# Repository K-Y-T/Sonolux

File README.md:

# Sonolux

Sonolux is an ongoing personal engineering project exploring the intersection of analogue electronics, embedded systems, signal processing, and software for music visualisation.

Originally inspired by a university assignment involving a three-band analogue frequency display, the project has since evolved into a broader platform for developing hardware and software related to audio signal analysis and visualisation.

---

## Current Status

The repository currently contains:

- Sound2Light prototype (breadboard implementation)
- Sonolux V1 analogue hardware design
- Circuit schematics
- PCB design files

The project is under active development and will continue to evolve throughout my undergraduate studies.

---

## Project Goals

Current long-term objectives include:

- Five-band analogue frequency visualisation
- Analogue Speaker system
- Custom PCB design
- Embedded control and power management
- Bluetooth audio integration
- JUCE-based desktop software

## What it uses

Current Development Areas

- Analogue Electronics
- PCB Design
- Autodesk Fusion
- Multisim

Future Development

- Embedded C/C++
- ESP32
- JUCE
- Digital Signal Processing

---

## Project Philosophy

Rather than being treated as a single coursework project, Sonolux serves as a long-term engineering platform through which I explore progressively more advanced concepts in electronics, embedded systems, and audio technology.

---

## Status

🟡 Active Development

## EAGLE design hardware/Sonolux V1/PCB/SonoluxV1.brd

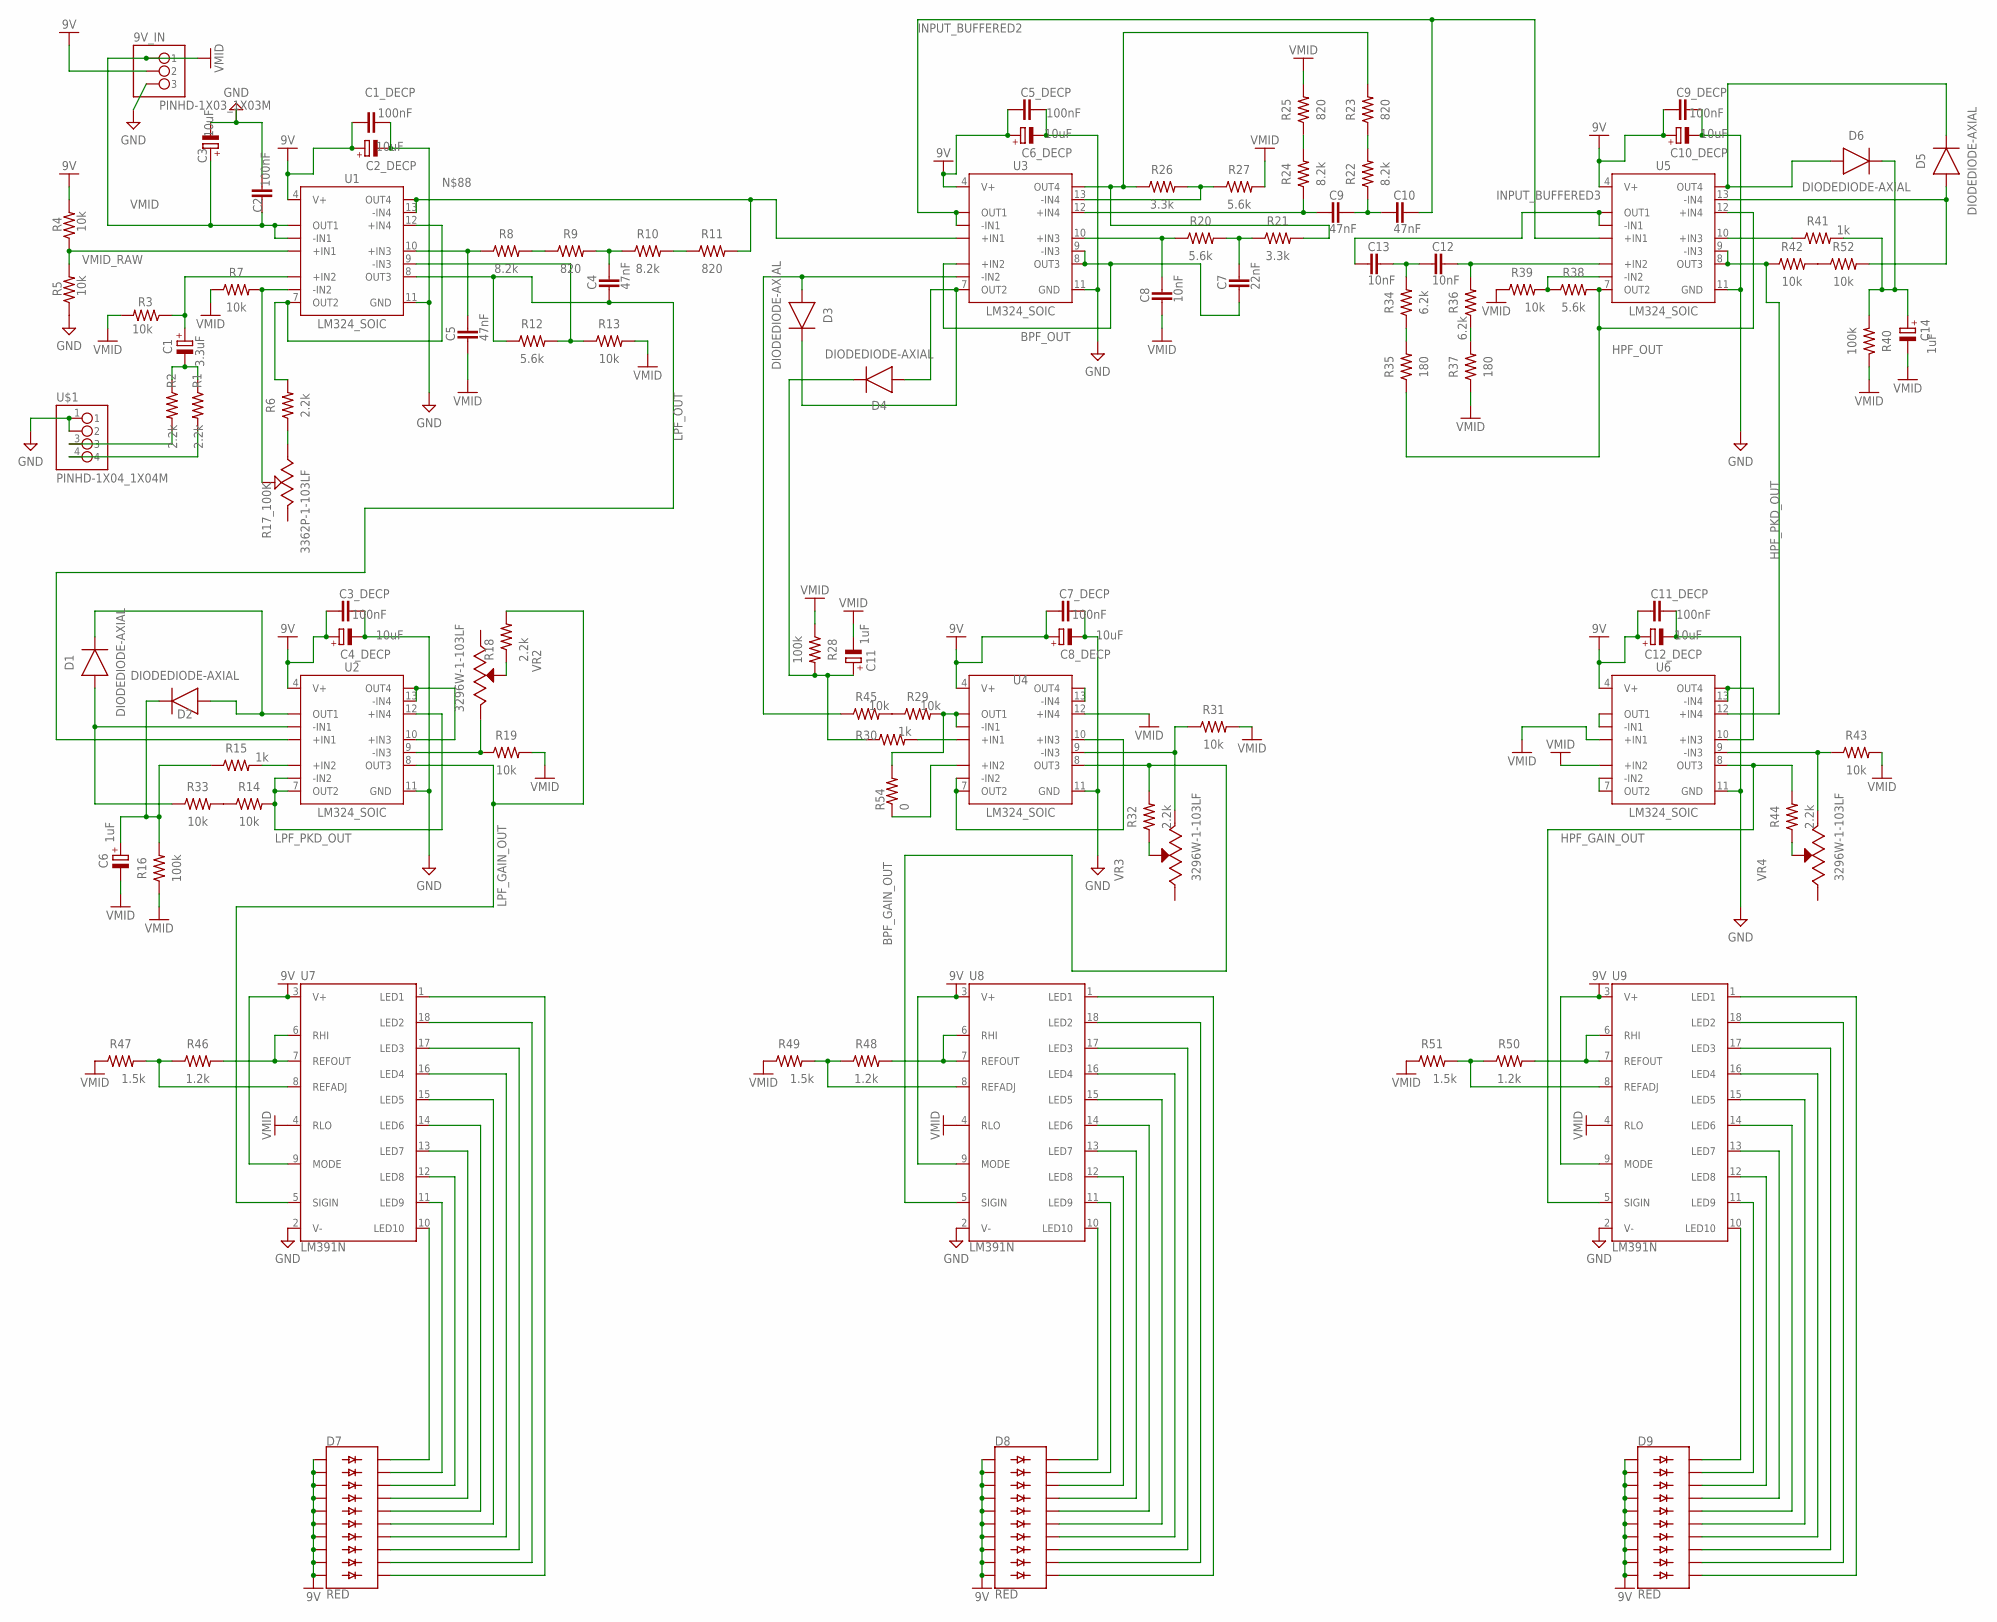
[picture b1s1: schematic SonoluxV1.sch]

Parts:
9V_IN: PINHD-1X03_1X03M; 1X03
C1: 3.3uF; CAPPRD254W65D500H1150B
C1_DECP, C2, C3_DECP, C5_DECP, C7_DECP, C9_DECP, C11_DECP: 100nF; CAP-THRU-2.54MM
C2_DECP, C3, C4_DECP, C6_DECP, C8_DECP, C10_DECP, C12_DECP: 10uF; CAPPRD254W65D500H1150B
C4, C5, C9, C10: 47nF; CAP-THRU-2.54MM
C6, C11, C14: 1uF; CAPPRD254W65D500H1150B
C7: 22nF; CAP-THRU-2.54MM
C8, C12, C13: 10nF; CAP-THRU-2.54MM
D1, D2, D3, D4, D5, D6: DIODEDIODE-AXIAL; DIODE-AXIAL
D7, D8, D9: RED; LED_BARGRAPH_10
R1, R2, R6, R18, R32, R44: 2.2k; RESAD724W46L381D178B
R3, R4, R5, R7, R13, R14, R19, R29, R31, R33, R39, R42, R43, R45, R52: 10k; RESAD724W46L381D178B
R8, R10, R22, R24: 8.2k; RESAD724W46L381D178B
R9, R11, R23, R25: 820; RESAD724W46L381D178B
R12, R20, R27, R38: 5.6k; RESAD724W46L381D178B
R15, R30, R41: 1k; RESAD724W46L381D178B
R16, R28, R40: 100k; RESAD724W46L381D178B
R17_100K: 3362P-1-103LF
R21, R26: 3.3k; RESAD724W46L381D178B
R34, R36: 6.2k; RESAD724W46L381D178B
R35, R37: 180; RESAD724W46L381D178B
R46, R48, R50: 1.2k; RESAD724W46L381D178B
R47, R49, R51: 1.5k; RESAD724W46L381D178B
R54: 0; RESAD724W46L381D178B
U1, U2, U3, U4, U5, U6: LM324_SOIC; SOIC127P600X175-14N
U7, U8, U9: LM391N; DIL18
U$1: PINHD-1X04_1X04M; 1X04
VR2, VR3, VR4: 3296W-1-103LF; TRIM_3296W-1-103LF

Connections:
9V: 9V_IN.2, C1_DECP.2, C2_DECP.1 (+), C3_DECP.2, C4_DECP.1 (+), C5_DECP.2, C6_DECP.1 (+), C7_DECP.2, C8_DECP.1 (+), C9_DECP.2, C10_DECP.1 (+), C11_DECP.2, C12_DECP.1 (+), D7.1 (A), D7.2 (A1), D7.3 (A2), D7.4 (A3), D7.5 (A4), D7.6 (A5), D7.7 (A6), D7.8 (A7), D7.9 (A8), D7.10 (A9), D8.1 (A), D8.2 (A1), D8.3 (A2), D8.4 (A3), D8.5 (A4), D8.6 (A5), D8.7 (A6), D8.8 (A7), D8.9 (A8), D8.10 (A9), D9.1 (A), D9.2 (A1), D9.3 (A2), D9.4 (A3), D9.5 (A4), D9.6 (A5), D9.7 (A6), D9.8 (A7), D9.9 (A8), D9.10 (A9), R4.2, U1.4 (V+), U2.4 (V+), U3.4 (V+), U4.4 (V+), U5.4 (V+), U6.4 (V+), U7.3 (V+), U7.9 (MODE), U8.3 (V+), U8.9 (MODE), U9.3 (V+), U9.9 (MODE)
BPF_GAIN_OUT: R32.2, U4.8 (OUT3), U8.5 (SIGIN)
BPF_OUT: C7.2, U3.5 (+IN2), U3.8 (OUT3), U3.9 (-IN3)
BPF_PKD_OUT: R29.2, R54.2, U4.1 (OUT1), U4.2 (-IN1)
GND: 9V_IN.3, C1_DECP.1, C2.1, C2_DECP.2 (-), C3.2 (-), C3_DECP.1, C4_DECP.2 (-), C5_DECP.1, C6_DECP.2 (-), C7_DECP.1, C8_DECP.2 (-), C9_DECP.1, C10_DECP.2 (-), C11_DECP.1, C12_DECP.2 (-), R5.1, U1.11 (GND), U2.11 (GND), U3.11 (GND), U4.11 (GND), U5.11 (GND), U6.11 (GND), U7.2 (V-), U8.2 (V-), U9.2 (V-), U$1.1, U$1.2
HPF_GAIN_OUT: R44.2, U6.8 (OUT3), U9.5 (SIGIN)
HPF_OUT: R35.1, R38.2, U5.7 (OUT2), U5.12 (+IN4)
HPF_PKD_OUT: R42.1, U5.8 (OUT3), U5.9 (-IN3), U6.12 (+IN4)
INPUT_BUFFERED2: C10.1, U3.1 (OUT1), U3.2 (-IN1), U5.3 (+IN1)
INPUT_BUFFERED3: C13.2, U5.1 (OUT1), U5.2 (-IN1)
INPUT_FILTERED: C1.1 (+), R3.1, U1.5 (+IN2)
INPUT_GAINED: R6.2, U1.7 (OUT2), U1.12 (+IN4)
INPUT_MONO: C1.2 (-), R1.1, R2.1
LPF_BUFFERED: U2.10 (+IN3), U2.13 (-IN4), U2.14 (OUT4)
LPF_GAIN_OUT: R18.2, U2.8 (OUT3), U7.5 (SIGIN)
LPF_OUT: C4.2, R12.1, U1.8 (OUT3), U2.3 (+IN1)
LPF_PKD_OUT: R14.2, U2.6 (-IN2), U2.7 (OUT2), U2.12 (+IN4)
unnamed: R6.1, R17_100K.3
unnamed: R7.2, R17_100K.2, U1.6 (-IN2)
unnamed: C5.1, R8.1, U1.10 (+IN3)
unnamed: R8.2, R9.1
unnamed: C4.1, R9.2, R10.1
unnamed: R10.2, R11.1
unnamed: D1.2 (C), D2.1 (A), U2.1 (OUT1)
unnamed: R12.2, R13.1, U1.9 (-IN3)
unnamed: D1.1 (A), R33.1, U2.2 (-IN1)
unnamed: C9.1, C10.2, R22.1
unnamed: C6.1 (+), D2.2 (C), R15.1, R16.2
unnamed: R15.2, U2.5 (+IN2)
unnamed: C8.1, R20.1, U3.10 (+IN3)
unnamed: D5.1 (A), R52.2, U5.13 (-IN4)
unnamed: C7.1, R20.2, R21.1
unnamed: R18.1, VR2.2 (WIPER)
unnamed: R21.2, R23.2, R26.1, U3.14 (OUT4)
unnamed: C9.2, R24.1, U3.12 (+IN4)
unnamed: R22.2, R23.1
unnamed: R24.2, R25.1
unnamed: R26.2, R27.1, U3.13 (-IN4)
unnamed: D3.1 (A), R45.1, U3.6 (-IN2)
unnamed: D3.2 (C), D4.1 (A), U3.7 (OUT2)
unnamed: C11.1 (+), D4.2 (C), R28.2, R30.1
unnamed: R32.1, VR3.2 (WIPER)
unnamed: R30.2, U4.3 (+IN1)
unnamed: U4.6 (-IN2), U4.7 (OUT2), U4.10 (+IN3)
unnamed: R31.1, U4.9 (-IN3), VR3.3 (CW)
unnamed: R38.1, R39.2, U5.6 (-IN2)
unnamed: C12.2, C13.1, R34.2
unnamed: R34.1, R35.2
unnamed: R36.1, R37.2
unnamed: C12.1, R36.2, U5.5 (+IN2)
unnamed: D5.2 (C), D6.1 (A), U5.14 (OUT4)
unnamed: C14.1 (+), D6.2 (C), R40.2, R41.2
unnamed: R46.2, U7.6 (RHI), U7.7 (REFOUT)
unnamed: R41.1, U5.10 (+IN3)
unnamed: U6.10 (+IN3), U6.13 (-IN4), U6.14 (OUT4)
unnamed: R44.1, VR4.2 (WIPER)
unnamed: R43.1, U6.9 (-IN3), VR4.3 (CW)
unnamed: R46.1, R47.2, U7.8 (REFADJ)
unnamed: D7.20 (C), U7.10 (LED10)
unnamed: D7.19 (C1), U7.11 (LED9)
unnamed: D7.18 (C2), U7.12 (LED8)
unnamed: D7.17 (C3), U7.13 (LED7)
unnamed: D7.16 (C4), U7.14 (LED6)
unnamed: D7.15 (C5), U7.15 (LED5)
unnamed: D7.14 (C6), U7.16 (LED4)
unnamed: D7.13 (C7), U7.17 (LED3)
unnamed: D7.12 (C8), U7.18 (LED2)
unnamed: D7.11 (C9), U7.1 (LED1)
unnamed: R48.2, U8.6 (RHI), U8.7 (REFOUT)
unnamed: R48.1, R49.2, U8.8 (REFADJ)
unnamed: D8.20 (C), U8.10 (LED10)
unnamed: D8.19 (C1), U8.11 (LED9)
unnamed: D8.18 (C2), U8.12 (LED8)
unnamed: D8.17 (C3), U8.13 (LED7)
unnamed: D8.16 (C4), U8.14 (LED6)
unnamed: D8.15 (C5), U8.15 (LED5)
unnamed: D8.14 (C6), U8.16 (LED4)
unnamed: D8.13 (C7), U8.17 (LED3)
unnamed: D8.12 (C8), U8.18 (LED2)
unnamed: D8.11 (C9), U8.1 (LED1)
unnamed: R50.2, U9.6 (RHI), U9.7 (REFOUT)
unnamed: R50.1, R51.2, U9.8 (REFADJ)
unnamed: D9.20 (C), U9.10 (LED10)
unnamed: D9.19 (C1), U9.11 (LED9)
unnamed: D9.18 (C2), U9.12 (LED8)
unnamed: D9.17 (C3), U9.13 (LED7)
unnamed: D9.16 (C4), U9.14 (LED6)
unnamed: D9.15 (C5), U9.15 (LED5)
unnamed: D9.14 (C6), U9.16 (LED4)
unnamed: D9.13 (C7), U9.17 (LED3)
unnamed: D9.12 (C8), U9.18 (LED2)
unnamed: D9.11 (C9), U9.1 (LED1)
unnamed: R14.1, R33.2
unnamed: R29.1, R45.2
unnamed: R42.2, R52.1
unnamed: U4.13 (-IN4), U4.14 (OUT4)
unnamed: U6.1 (OUT1), U6.2 (-IN1)
unnamed: U6.6 (-IN2), U6.7 (OUT2)
unnamed: R2.2, U$1.3
unnamed: R1.2, U$1.4
unnamed: R54.1, U4.5 (+IN2)
unnamed: R19.1, U2.9 (-IN3), VR2.3 (CW)
unnamed: R11.2, U1.13 (-IN4), U1.14 (OUT4), U3.3 (+IN1)
VMID: 9V_IN.1, C2.2, C3.1 (+), C5.2, C6.2 (-), C8.2, C11.2 (-), C14.2 (-), R3.2, R7.1, R13.2, R16.1, R19.2, R25.2, R27.2, R28.1, R31.2, R37.1, R39.1, R40.1, R43.2, R47.1, R49.1, R51.1, U1.1 (OUT1), U1.2 (-IN1), U4.12 (+IN4), U6.3 (+IN1), U6.5 (+IN2), U7.4 (RLO), U8.4 (RLO), U9.4 (RLO)
VMID_RAW: R4.1, R5.2, U1.3 (+IN1)

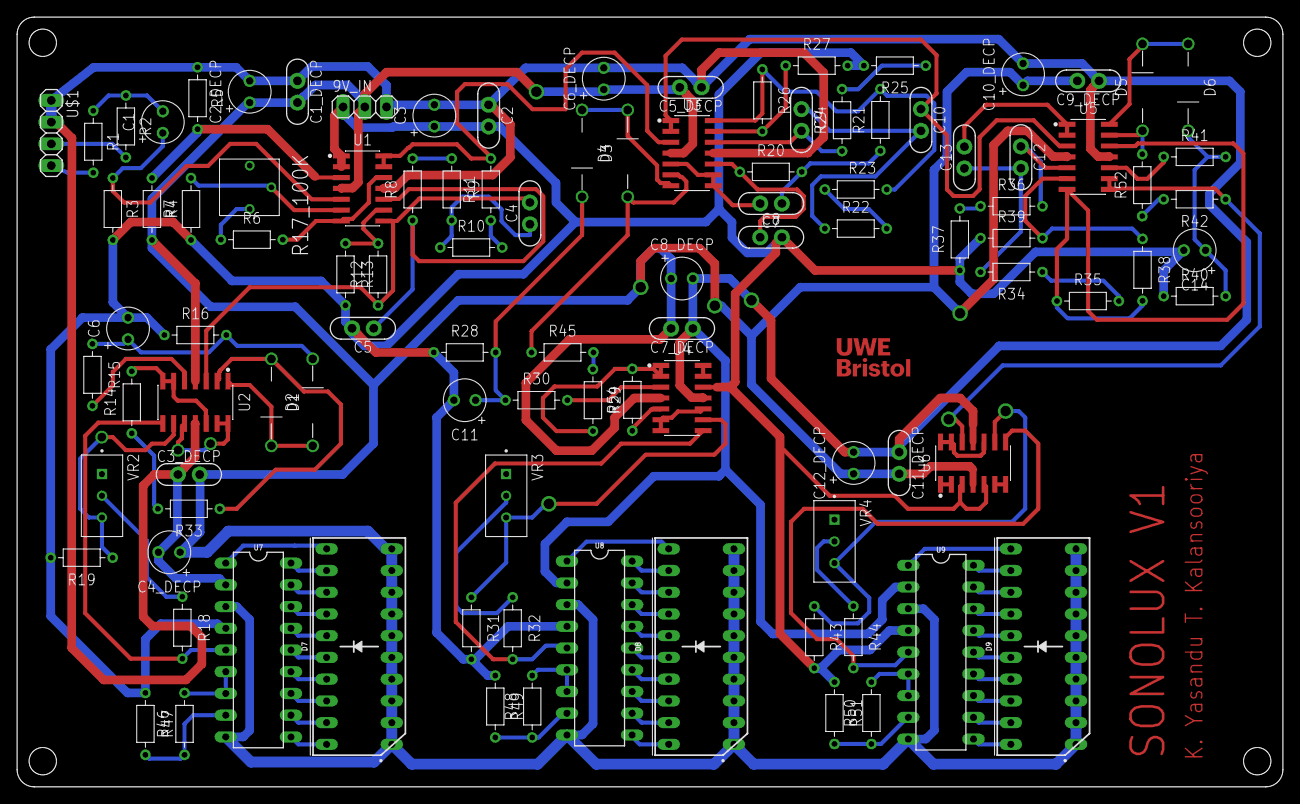
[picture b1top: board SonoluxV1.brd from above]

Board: 2 copper layers, 148.0 x 90.0 mm, 102 parts (0 on the bottom side), 105 nets.

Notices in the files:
parts and their libraries:
SparkFun-LED: Licensing: Creative Commons ShareAlike 4.0 International - https://creativecommons.org/licenses/by-sa/4.0
